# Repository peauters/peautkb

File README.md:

# Peautkb

## Intro
This is my first foray into custom built mechanical keyboards. I designed this as a mini project to get into pcb design and embedded code in `rust`. 

It has been awesome.

## Details
This board takes a lot of inspiration from the [Corne](https://github.com/foostan/crkbd) and [Kyria](https://blog.splitkb.com/blog/introducing-the-kyria) boards. 

I really liked the 3 rows from the Corne, as well as the rotaries from the Kyria. I wanted a single row thumb cluster and a column stager that fitted my hands. In then end, I ended up with what is in this repo.

## Firmware
Before I really had much info about open source keyboards, I decided I wanted to write my own firmware in `rust`. A well supported chip and board is the (WeAct MiniSTM32F4x1)[https://github.com/WeActTC/MiniSTM32F4x1] aka "the blackpill".

This board has a different footprint to a Pro Micro, which in hindsight has probably made this board very niche. I know of other blackpill boards (like the [Grandiceps](https://shop.tokas.co.uk/product/grandiceps-split-keyboard-kit/?v=79cba1185463)), but they seem limited at the moment.

The firmware is custom, written in `rust` using the [keyberon](https://github.com/TeXitoi/keyberon) as a base. At the moment, it manages communication between each side, the ssd1306 displays and has code to enable media keys in a second usb HID report. The most important feature is bongo cat animated displays. Thank you to [dancarrol](https://github.com/dancarroll/qmk-bongo) for the inspiration.

### How to build the firmware
- Install rust (see [here](https://www.rust-lang.org/tools/install))
- Install the compile target for the black-pills `rustup target install thumbv7em-none-eabihf`
- Install binutils to create a binary file `cargo install cargo-binutils` and `rustup component add llvm-tools-preview` 
- Build the binary `cargo objcopy --release -- -O binary out.bin`
- Put the black-pill in dfu boot loader. Hold the `NRST` and `BOOT0` buttons at the same time, then let go of `NRST` while still holding `BOOT0` button for a second longer.
- Check you can see it with `lsusb`
- Flash with dfu-util or similar
- Repeat for both sides

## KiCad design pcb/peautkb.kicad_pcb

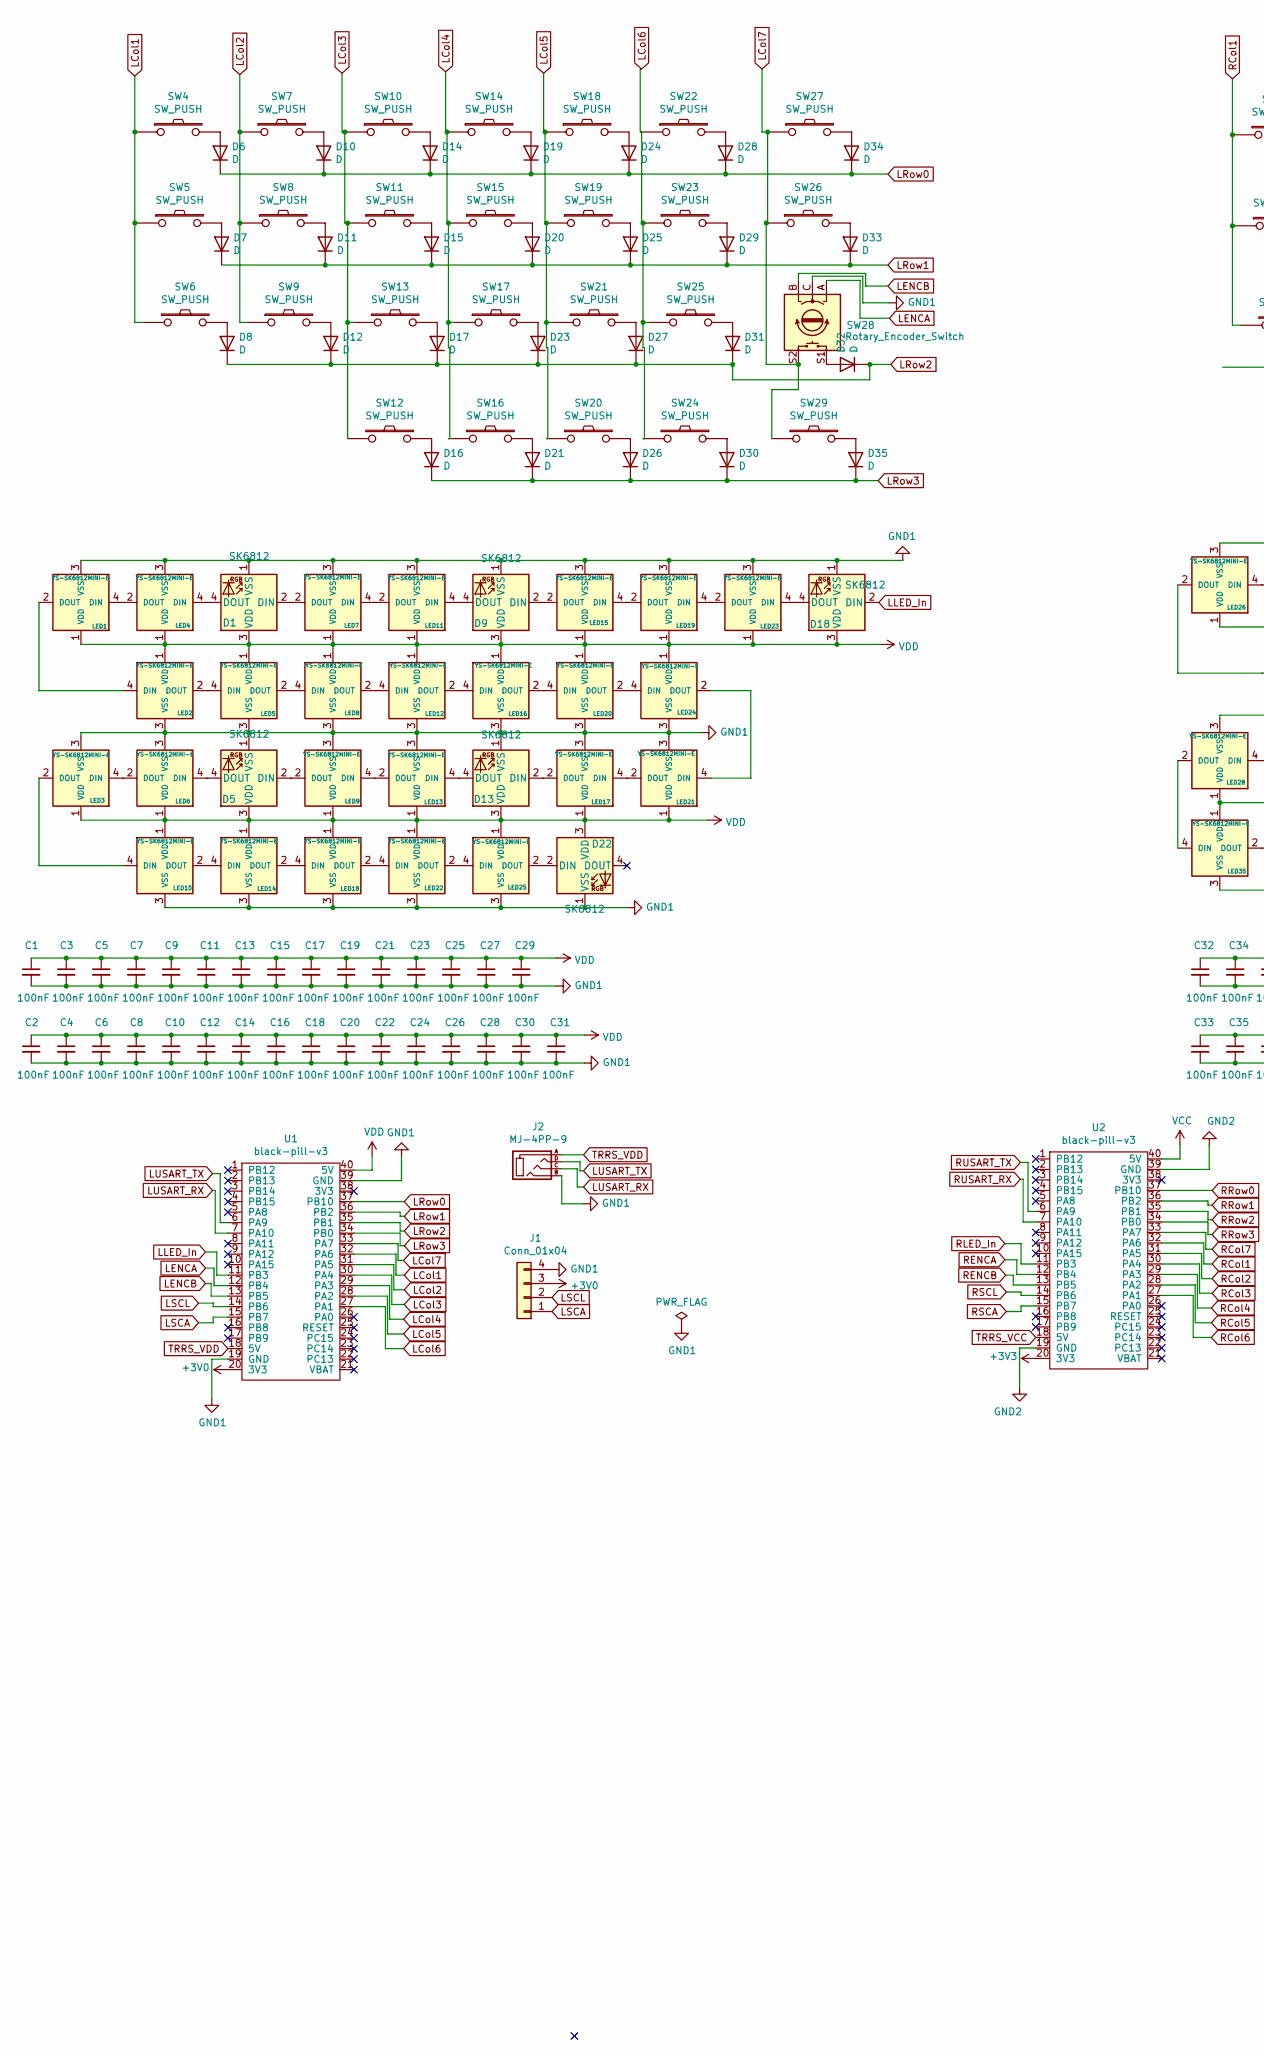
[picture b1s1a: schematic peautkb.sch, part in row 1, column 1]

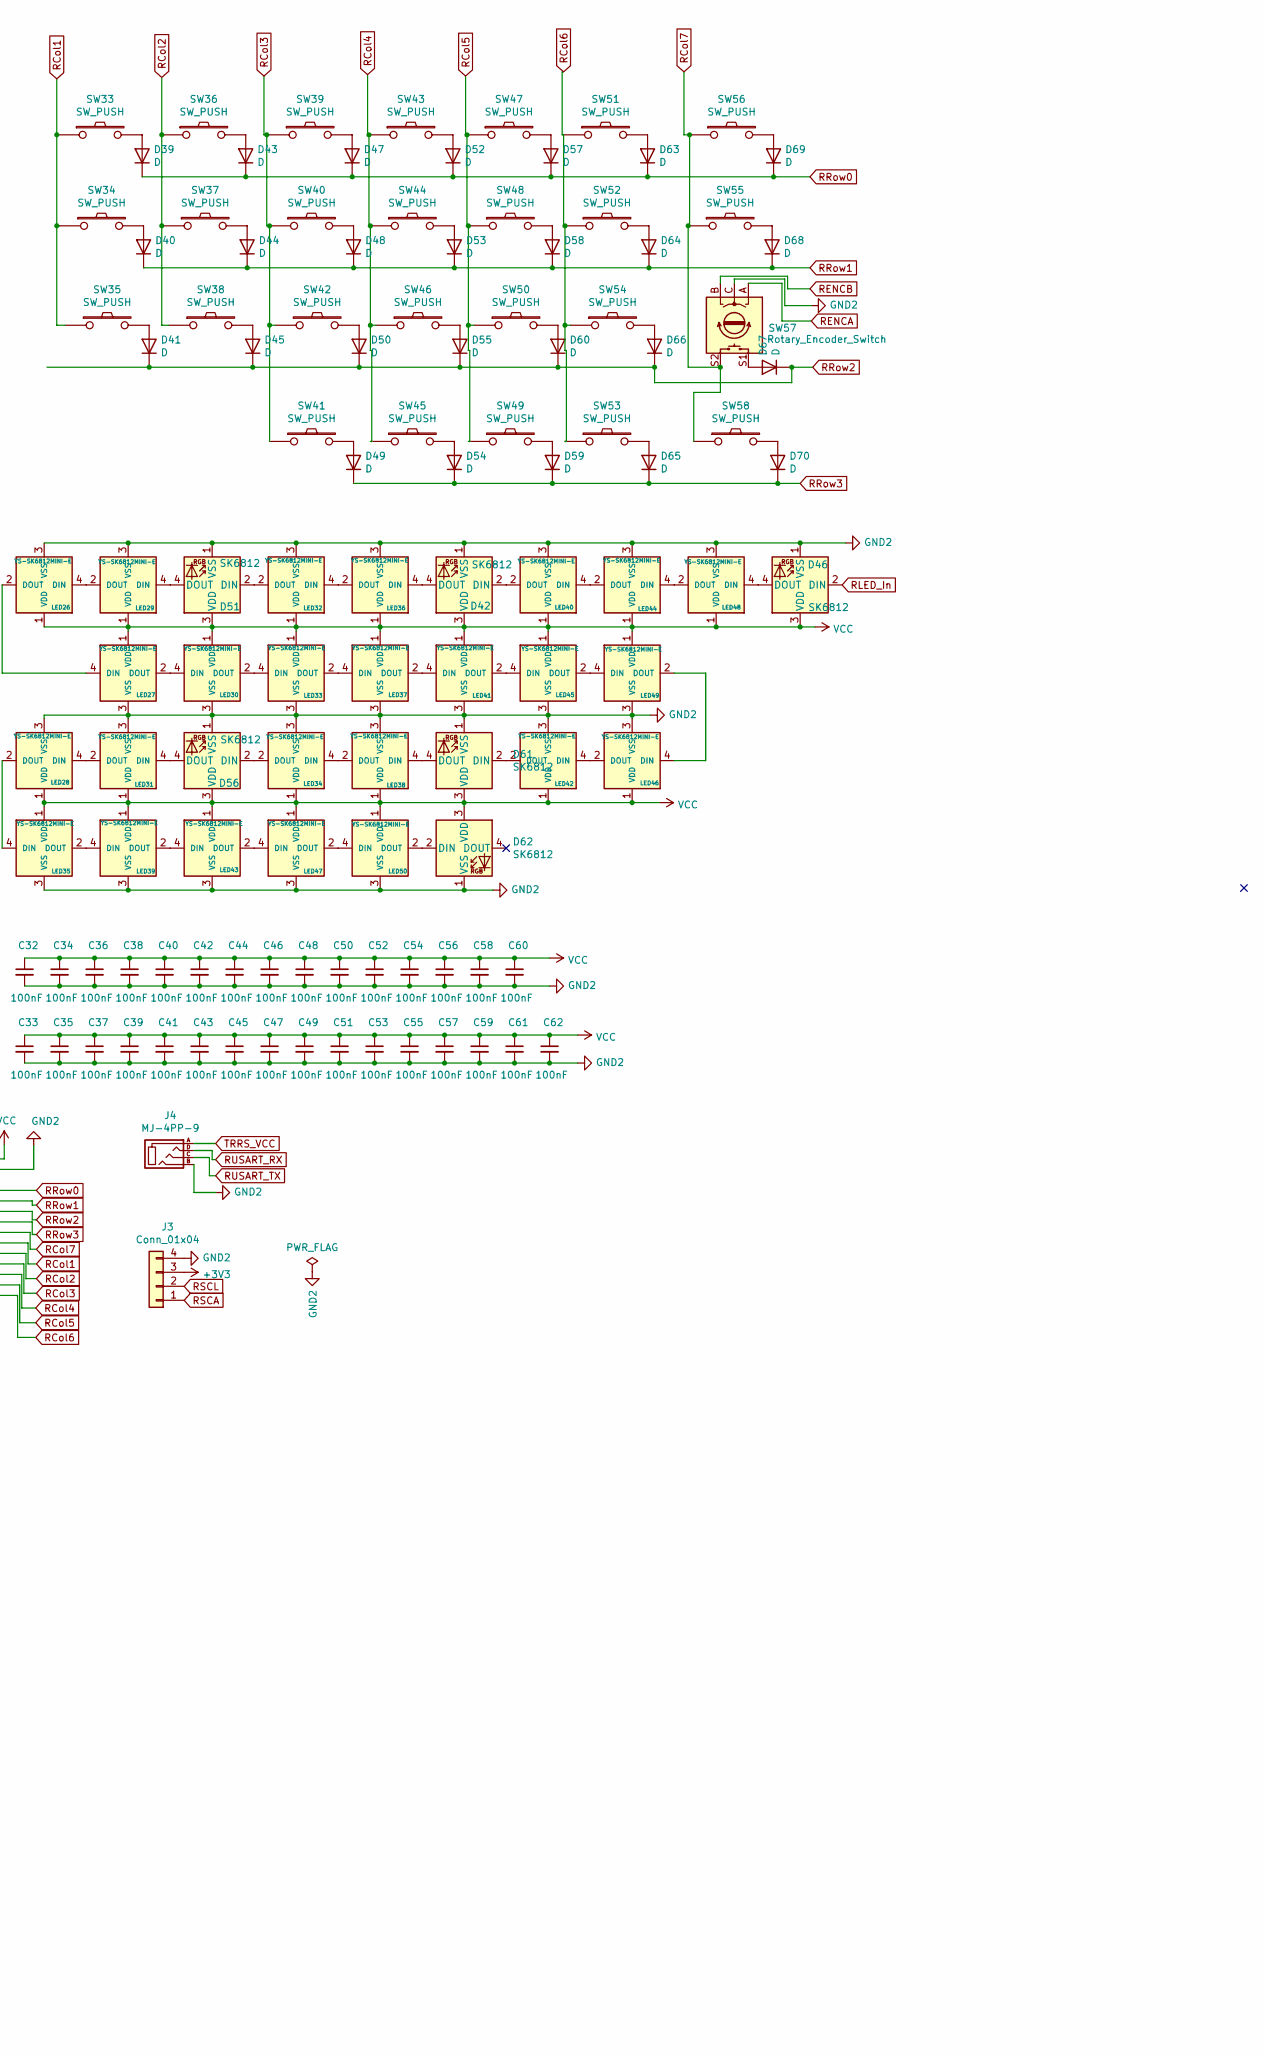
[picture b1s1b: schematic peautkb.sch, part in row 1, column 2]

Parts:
C1, C2, C3, C4, C5, C6, C7, C8, C9, C10, C11, C12, C13, C14, C15, C16, C17, C18, C19, C20, C21, C22, C23, C24, C25, C26, C27, C28, C29, C30, C31, C32, C33, C34, C35, C36, C37, C38, C39, C40, C41, C42, C43, C44, C45, C46, C47, C48, C49, C50, C51, C52, C53, C54, C55, C56, C57, C58, C59, C60, C61, C62: 100nF; C_0805_2012Metric_Pad1.18x1.45mm_HandSolder
D1, D5, D9, D13, D18, D22, D42, D46, D51, D56, D61, D62: SK6812; LED_SK6812_PLCC4_5.0x5.0mm_P3.2mm
D6, D7, D8, D10, D11, D12, D14, D15, D16, D17, D19, D20, D21, D23, D24, D25, D26, D27, D28, D29, D30, D31, D32, D33, D34, D35, D39, D40, D41, D43, D44, D45, D47, D48, D49, D50, D52, D53, D54, D55, D57, D58, D59, D60, D63, D64, D65, D66, D67, D68, D69, D70: D; D3_SMD_v2
J1, J3: Conn_01x04; OLED_1side
J2, J4: MJ-4PP-9
LED1, LED2, LED3, LED4, LED5, LED6, LED7, LED8, LED9, LED10, LED11, LED12, LED13, LED14, LED15, LED16, LED17, LED18, LED19, LED20, LED21, LED22, LED23, LED24, LED25, LED26, LED27, LED28, LED29, LED30, LED31, LED32, LED33, LED34, LED35, LED36, LED37, LED38, LED39, LED40, LED41, LED42, LED43, LED44, LED45, LED46, LED47, LED48, LED49, LED50: YS-SK6812MINI-E
SW4, SW5, SW6, SW7, SW8, SW9, SW10, SW11, SW12, SW13, SW14, SW15, SW16, SW17, SW18, SW19, SW20, SW21, SW22, SW23, SW24, SW25, SW26, SW27, SW29, SW33, SW34, SW35, SW36, SW37, SW38, SW39, SW40, SW41, SW42, SW43, SW44, SW45, SW46, SW47, SW48, SW49, SW50, SW51, SW52, SW53, SW54, SW55, SW56, SW58: SW_PUSH; CherryMX_Hotswap
SW28, SW57: Rotary_Encoder_Switch; RotaryEncoder_Alps_EC11E-Switch_Vertical_H20mm
U1, U2: black-pill-v3

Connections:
+3V0: J1.3, U1.20 (3V3)
+3V3: J3.3, U2.20 (3V3)
GND1: C1.2, C2.2, C3.2, C4.2, C5.2, C6.2, C7.2, C8.2, C9.2, C10.2, C11.2, C12.2, C13.2, C14.2, C15.2, C16.2, C17.2, C18.2, C19.2, C20.2, C21.2, C22.2, C23.2, C24.2, C25.2, C26.2, C27.2, C28.2, C29.2, C30.2, C31.2, D1.1 (VSS), D5.1 (VSS), D9.1 (VSS), D13.1 (VSS), D18.1 (VSS), D22.1 (VSS), J1.4, J2.B, LED1.3 (VSS), LED2.3 (VSS), LED3.3 (VSS), LED4.3 (VSS), LED5.3 (VSS), LED6.3 (VSS), LED7.3 (VSS), LED8.3 (VSS), LED9.3 (VSS), LED10.3 (VSS), LED11.3 (VSS), LED12.3 (VSS), LED13.3 (VSS), LED14.3 (VSS), LED15.3 (VSS), LED16.3 (VSS), LED17.3 (VSS), LED18.3 (VSS), LED19.3 (VSS), LED20.3 (VSS), LED21.3 (VSS), LED22.3 (VSS), LED23.3 (VSS), LED24.3 (VSS), LED25.3 (VSS), SW28.C, U1.19 (GND), U1.39 (GND)
GND2: C32.2, C33.2, C34.2, C35.2, C36.2, C37.2, C38.2, C39.2, C40.2, C41.2, C42.2, C43.2, C44.2, C45.2, C46.2, C47.2, C48.2, C49.2, C50.2, C51.2, C52.2, C53.2, C54.2, C55.2, C56.2, C57.2, C58.2, C59.2, C60.2, C61.2, C62.2, D42.1 (VSS), D46.1 (VSS), D51.1 (VSS), D56.1 (VSS), D61.1 (VSS), D62.1 (VSS), J3.4, J4.B, LED26.3 (VSS), LED27.3 (VSS), LED28.3 (VSS), LED29.3 (VSS), LED30.3 (VSS), LED31.3 (VSS), LED32.3 (VSS), LED33.3 (VSS), LED34.3 (VSS), LED35.3 (VSS), LED36.3 (VSS), LED37.3 (VSS), LED38.3 (VSS), LED39.3 (VSS), LED40.3 (VSS), LED41.3 (VSS), LED42.3 (VSS), LED43.3 (VSS), LED44.3 (VSS), LED45.3 (VSS), LED46.3 (VSS), LED47.3 (VSS), LED48.3 (VSS), LED49.3 (VSS), LED50.3 (VSS), SW57.C, U2.19 (GND), U2.39 (GND)
LCol1: SW4.1, SW5.1, SW6.1, U1.32 (PA6)
LCol2: SW7.1, SW8.1, SW9.1, U1.31 (PA5)
LCol3: SW10.1, SW11.1, SW12.1, SW13.1, U1.30 (PA4)
LCol4: SW14.1, SW15.1, SW16.1, SW17.1, U1.29 (PA3)
LCol5: SW18.1, SW19.1, SW20.1, SW21.1, U1.28 (PA2)
LCol6: SW22.1, SW23.1, SW24.1, SW25.1, U1.27 (PA1)
LCol7: SW26.1, SW27.1, SW28.S2, SW29.1, U1.33 (PA7)
LENCA: SW28.A, U1.12 (PB4)
LENCB: SW28.B, U1.13 (PB5)
LLED_In: D18.2 (DIN), U1.11 (PB3)
LRow0: D6.1 (K), D10.1 (K), D14.1 (K), D19.1 (K), D24.1 (K), D28.1 (K), D34.1 (K), U1.37 (PB10)
LRow1: D7.1 (K), D11.1 (K), D15.1 (K), D20.1 (K), D25.1 (K), D29.1 (K), D33.1 (K), U1.36 (PB2)
LRow2: D8.1 (K), D12.1 (K), D17.1 (K), D23.1 (K), D27.1 (K), D31.1 (K), D32.1 (K), U1.35 (PB1)
LRow3: D16.1 (K), D21.1 (K), D26.1 (K), D30.1 (K), D35.1 (K), U1.34 (PB0)
LSCA: J1.1, U1.15 (PB7)
LSCL: J1.2, U1.14 (PB6)
LUSART_RX: J2.C, U1.7 (PA10)
LUSART_TX: J2.D, U1.6 (PA9)
unnamed: D1.2 (DIN), LED7.2 (DOUT)
unnamed: D1.4 (DOUT), LED4.4 (DIN)
unnamed: D5.2 (DIN), LED9.2 (DOUT)
unnamed: D5.4 (DOUT), LED6.4 (DIN)
unnamed: D6.2 (A), SW4.2
unnamed: D7.2 (A), SW5.2
unnamed: D8.2 (A), SW6.2
unnamed: D9.2 (DIN), LED15.2 (DOUT)
unnamed: D9.4 (DOUT), LED11.4 (DIN)
unnamed: D10.2 (A), SW7.2
unnamed: D11.2 (A), SW8.2
unnamed: D12.2 (A), SW9.2
unnamed: D13.2 (DIN), LED17.2 (DOUT)
unnamed: D13.4 (DOUT), LED13.4 (DIN)
unnamed: D14.2 (A), SW10.2
unnamed: D15.2 (A), SW11.2
unnamed: D16.2 (A), SW12.2
unnamed: D17.2 (A), SW13.2
unnamed: D18.4 (DOUT), LED23.4 (DIN)
unnamed: D19.2 (A), SW14.2
unnamed: D20.2 (A), SW15.2
unnamed: D21.2 (A), SW16.2
unnamed: D22.2 (DIN), LED25.2 (DOUT)
unnamed: D23.2 (A), SW17.2
unnamed: D24.2 (A), SW18.2
unnamed: D25.2 (A), SW19.2
unnamed: D26.2 (A), SW20.2
unnamed: D27.2 (A), SW21.2
unnamed: D28.2 (A), SW22.2
unnamed: D29.2 (A), SW23.2
unnamed: D30.2 (A), SW24.2
unnamed: D31.2 (A), SW25.2
unnamed: D32.2 (A), SW28.S1
unnamed: D33.2 (A), SW26.2
unnamed: D34.2 (A), SW27.2
unnamed: D35.2 (A), SW29.2
unnamed: D39.2 (A), SW33.2
unnamed: D40.2 (A), SW34.2
unnamed: D41.2 (A), SW35.2
unnamed: D42.2 (DIN), LED40.2 (DOUT)
unnamed: D42.4 (DOUT), LED36.4 (DIN)
unnamed: D43.2 (A), SW36.2
unnamed: D44.2 (A), SW37.2
unnamed: D45.2 (A), SW38.2
unnamed: D46.4 (DOUT), LED48.4 (DIN)
unnamed: D47.2 (A), SW39.2
unnamed: D48.2 (A), SW40.2
unnamed: D49.2 (A), SW41.2
unnamed: D50.2 (A), SW42.2
unnamed: D51.2 (DIN), LED32.2 (DOUT)
unnamed: D51.4 (DOUT), LED29.4 (DIN)
unnamed: D52.2 (A), SW43.2
unnamed: D53.2 (A), SW44.2
unnamed: D54.2 (A), SW45.2
unnamed: D55.2 (A), SW46.2
unnamed: D56.2 (DIN), LED34.2 (DOUT)
unnamed: D56.4 (DOUT), LED31.4 (DIN)
unnamed: D57.2 (A), SW47.2
unnamed: D58.2 (A), SW48.2
unnamed: D59.2 (A), SW49.2
unnamed: D60.2 (A), SW50.2
unnamed: D61.2 (DIN), LED42.2 (DOUT)
unnamed: D61.4 (DOUT), LED38.4 (DIN)
unnamed: D62.2 (DIN), LED50.2 (DOUT)
unnamed: D63.2 (A), SW51.2
unnamed: D64.2 (A), SW52.2
unnamed: D65.2 (A), SW53.2
unnamed: D66.2 (A), SW54.2
unnamed: D67.2 (A), SW57.S1
unnamed: D68.2 (A), SW55.2
unnamed: D69.2 (A), SW56.2
unnamed: D70.2 (A), SW58.2
unnamed: LED1.2 (DOUT), LED2.4 (DIN)
unnamed: LED1.4 (DIN), LED4.2 (DOUT)
unnamed: LED2.2 (DOUT), LED5.4 (DIN)
unnamed: LED3.4 (DIN), LED6.2 (DOUT)
unnamed: LED5.2 (DOUT), LED8.4 (DIN)
unnamed: LED10.2 (DOUT), LED14.4 (DIN)
unnamed: LED3.2 (DOUT), LED10.4 (DIN)
unnamed: LED7.4 (DIN), LED11.2 (DOUT)
unnamed: LED12.2 (DOUT), LED16.4 (DIN)
unnamed: LED8.2 (DOUT), LED12.4 (DIN)
unnamed: LED9.4 (DIN), LED13.2 (DOUT)
unnamed: LED14.2 (DOUT), LED18.4 (DIN)
unnamed: LED15.4 (DIN), LED19.2 (DOUT)
unnamed: LED16.2 (DOUT), LED20.4 (DIN)
unnamed: LED17.4 (DIN), LED21.2 (DOUT)
unnamed: LED18.2 (DOUT), LED22.4 (DIN)
unnamed: LED19.4 (DIN), LED23.2 (DOUT)
unnamed: LED20.2 (DOUT), LED24.4 (DIN)
unnamed: LED21.4 (DIN), LED24.2 (DOUT)
unnamed: LED22.2 (DOUT), LED25.4 (DIN)
unnamed: LED26.2 (DOUT), LED27.4 (DIN)
unnamed: LED26.4 (DIN), LED29.2 (DOUT)
unnamed: LED27.2 (DOUT), LED30.4 (DIN)
unnamed: LED28.2 (DOUT), LED35.4 (DIN)
unnamed: LED28.4 (DIN), LED31.2 (DOUT)
unnamed: LED30.2 (DOUT), LED33.4 (DIN)
unnamed: LED32.4 (DIN), LED36.2 (DOUT)
unnamed: LED33.2 (DOUT), LED37.4 (DIN)
unnamed: LED34.4 (DIN), LED38.2 (DOUT)
unnamed: LED35.2 (DOUT), LED39.4 (DIN)
unnamed: LED37.2 (DOUT), LED41.4 (DIN)
unnamed: LED39.2 (DOUT), LED43.4 (DIN)
unnamed: LED40.4 (DIN), LED44.2 (DOUT)
unnamed: LED41.2 (DOUT), LED45.4 (DIN)
unnamed: LED42.4 (DIN), LED46.2 (DOUT)
unnamed: LED43.2 (DOUT), LED47.4 (DIN)
unnamed: LED44.4 (DIN), LED48.2 (DOUT)
unnamed: LED45.2 (DOUT), LED49.4 (DIN)
unnamed: LED46.4 (DIN), LED49.2 (DOUT)
unnamed: LED47.2 (DOUT), LED50.4 (DIN)
RCol1: SW33.1, SW34.1, SW35.1, U2.32 (PA6)
RCol2: SW36.1, SW37.1, SW38.1, U2.31 (PA5)
RCol3: SW39.1, SW40.1, SW41.1, SW42.1, U2.30 (PA4)
RCol4: SW43.1, SW44.1, SW45.1, SW46.1, U2.29 (PA3)
RCol5: SW47.1, SW48.1, SW49.1, SW50.1, U2.28 (PA2)
RCol6: SW51.1, SW52.1, SW53.1, SW54.1, U2.27 (PA1)
RCol7: SW55.1, SW56.1, SW57.S2, SW58.1, U2.33 (PA7)
RENCA: SW57.A, U2.12 (PB4)
RENCB: SW57.B, U2.13 (PB5)
RLED_In: D46.2 (DIN), U2.11 (PB3)
RRow0: D39.1 (K), D43.1 (K), D47.1 (K), D52.1 (K), D57.1 (K), D63.1 (K), D69.1 (K), U2.37 (PB10)
RRow1: D40.1 (K), D44.1 (K), D48.1 (K), D53.1 (K), D58.1 (K), D64.1 (K), D68.1 (K), U2.36 (PB2)
RRow2: D41.1 (K), D45.1 (K), D50.1 (K), D55.1 (K), D60.1 (K), D66.1 (K), D67.1 (K), U2.35 (PB1)
RRow3: D49.1 (K), D54.1 (K), D59.1 (K), D65.1 (K), D70.1 (K), U2.34 (PB0)
RSCA: J3.1, U2.15 (PB7)
RSCL: J3.2, U2.14 (PB6)
RUSART_RX: J4.D, U2.7 (PA10)
RUSART_TX: J4.C, U2.6 (PA9)
TRRS_VCC: J4.A, U2.18 (5V)
TRRS_VDD: J2.A, U1.18 (5V)
VCC: C32.1, C33.1, C34.1, C35.1, C36.1, C37.1, C38.1, C39.1, C40.1, C41.1, C42.1, C43.1, C44.1, C45.1, C46.1, C47.1, C48.1, C49.1, C50.1, C51.1, C52.1, C53.1, C54.1, C55.1, C56.1, C57.1, C58.1, C59.1, C60.1, C61.1, C62.1, D42.3 (VDD), D46.3 (VDD), D51.3 (VDD), D56.3 (VDD), D61.3 (VDD), D62.3 (VDD), LED26.1 (VDD), LED27.1 (VDD), LED28.1 (VDD), LED29.1 (VDD), LED30.1 (VDD), LED31.1 (VDD), LED32.1 (VDD), LED33.1 (VDD), LED34.1 (VDD), LED35.1 (VDD), LED36.1 (VDD), LED37.1 (VDD), LED38.1 (VDD), LED39.1 (VDD), LED40.1 (VDD), LED41.1 (VDD), LED42.1 (VDD), LED43.1 (VDD), LED44.1 (VDD), LED45.1 (VDD), LED46.1 (VDD), LED47.1 (VDD), LED48.1 (VDD), LED49.1 (VDD), LED50.1 (VDD), U2.40 (5V)
VDD: C1.1, C2.1, C3.1, C4.1, C5.1, C6.1, C7.1, C8.1, C9.1, C10.1, C11.1, C12.1, C13.1, C14.1, C15.1, C16.1, C17.1, C18.1, C19.1, C20.1, C21.1, C22.1, C23.1, C24.1, C25.1, C26.1, C27.1, C28.1, C29.1, C30.1, C31.1, D1.3 (VDD), D5.3 (VDD), D9.3 (VDD), D13.3 (VDD), D18.3 (VDD), D22.3 (VDD), LED1.1 (VDD), LED2.1 (VDD), LED3.1 (VDD), LED4.1 (VDD), LED5.1 (VDD), LED6.1 (VDD), LED7.1 (VDD), LED8.1 (VDD), LED9.1 (VDD), LED10.1 (VDD), LED11.1 (VDD), LED12.1 (VDD), LED13.1 (VDD), LED14.1 (VDD), LED15.1 (VDD), LED16.1 (VDD), LED17.1 (VDD), LED18.1 (VDD), LED19.1 (VDD), LED20.1 (VDD), LED21.1 (VDD), LED22.1 (VDD), LED23.1 (VDD), LED24.1 (VDD), LED25.1 (VDD), U1.40 (5V)

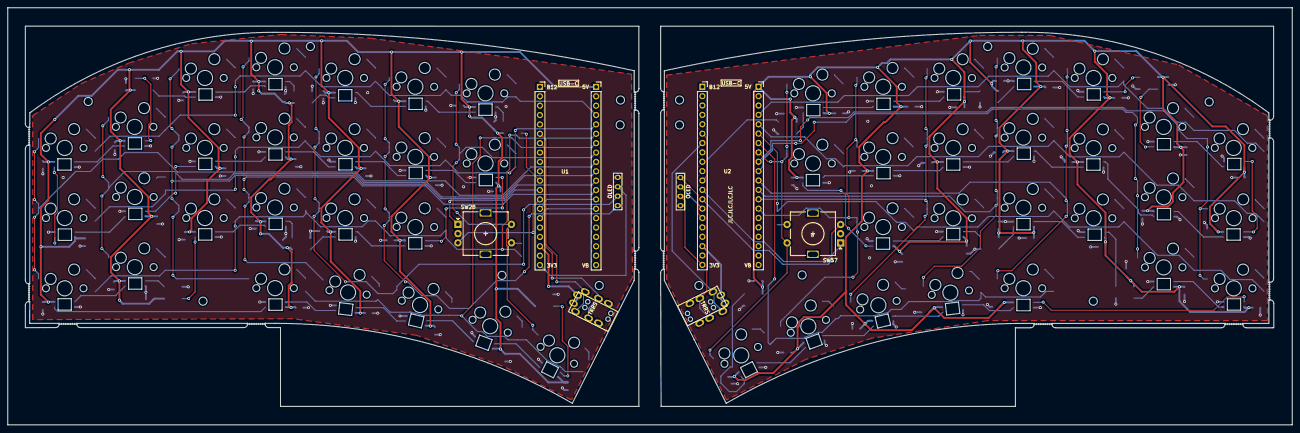
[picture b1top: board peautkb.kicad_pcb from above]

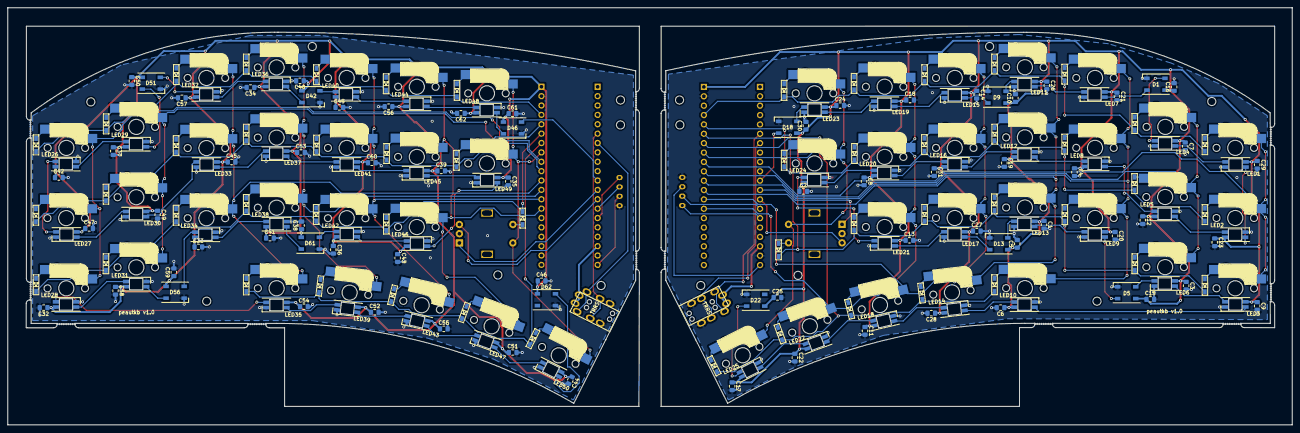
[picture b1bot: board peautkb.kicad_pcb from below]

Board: 2 copper layers, 348.0 x 113.0 mm, 248 parts (176 on the bottom side), 156 nets.

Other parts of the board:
Ref**: Val**; M2_HOLE_v2
Ref**#2, Ref**#3, Ref**#4, Ref**#5, Ref**#6, Ref**#7, Ref**#8, Ref**#9, Ref**#10, Ref**#11, Ref**#12, Ref**#13, Ref**#14: Val**; M2_HOLE_v2

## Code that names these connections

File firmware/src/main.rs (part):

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    const PID: u16 = 0x27db;

    pub struct Cols(
        gpioa::PA6<Input<PullUp>>,
        gpioa::PA5<Input<PullUp>>,
        gpioa::PA4<Input<PullUp>>,
        gpioa::PA3<Input<PullUp>>,
        gpioa::PA2<Input<PullUp>>,
        gpioa::PA1<Input<PullUp>>,
        gpioa::PA7<Input<PullUp>>,
    );
    impl_heterogenous_array! {
        Cols,
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        [0, 1, 2, 3, 4, 5, 6]
    }
    pub struct Rows(
        gpiob::PB10<Output<PushPull>>,
        gpiob::PB2<Output<PushPull>>,
        gpiob::PB1<Output<PushPull>>,
        gpiob::PB0<Output<PushPull>>,
    );
    impl_heterogenous_array! {
        Rows,
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        let tick_timer = timer::Timer::tim4(perfs.TIM4, 24.hz(), clocks);

        // I2C for SSD1306 display
        let pb6 = gpiob
            .pb6
            .into_alternate_af4()
            .internal_pull_up(true)
            .set_open_drain();
        let pb7 = gpiob
            .pb7
            .into_alternate_af4()
            .internal_pull_up(true)
            .set_open_drain();
        let display = OLED::new(perfs.I2C1, pb6, pb7, clocks);

        // Rotary encoder pins
        let pb4 = gpiob.pb4.into_pull_up_input();
        let mut pb5 = gpiob.pb5.into_pull_up_input();

        pb5.make_interrupt_source(&mut syscfg);
        pb5.enable_interrupt(&mut perfs.EXTI);
        pb5.trigger_on_edge(&mut perfs.EXTI, Edge::RISING_FALLING);

        let rotary = Rotary::new(pb4, pb5, (3, 0), (3, 1));

        // USB keyboard
        let usb = otg_fs::USB {
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            .build();

        // Inter-board comms
        let pa9 = gpioa.pa9.into_alternate_af7();
        let pa10 = gpioa.pa10.into_alternate_af7();

        let (tx, rx) = create_comms(perfs.USART1, pa9, pa10, clocks);

        // Keyberon setup
        let matrix = Matrix::new(
            Cols(
                gpioa.pa6.into_pull_up_input(),
                gpioa.pa5.into_pull_up_input(),
                gpioa.pa4.into_pull_up_input(),
                gpioa.pa3.into_pull_up_input(),
                gpioa.pa2.into_pull_up_input(),
                gpioa.pa1.into_pull_up_input(),
                gpioa.pa7.into_pull_up_input(),
            ),
            Rows(
                gpiob.pb10.into_push_pull_output(),
                gpiob.pb2.into_push_pull_output(),
                gpiob.pb1.into_push_pull_output(),
                gpiob.pb0.into_push_pull_output(),
            ),
        )
        .unwrap();
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
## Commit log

2021-03-27 before pcb layout
2021-03-27 removes extra col
2021-03-28 left side traces completed
2021-03-29 aadded decoup caps to LHS
2021-03-29 finished RHS
2021-03-30 generate gerbers
2021-03-31 added practice pads
2021-04-01 logo and final OLED placement
2021-04-02 pcb tweaks
2021-04-02 initial firmware with rtic timer working
2021-04-02 adds registering as a keyboard
2021-04-10 updated rotary encoder pins to avoid crystal
2021-04-11 LED working, usb hid working, display working (on reset), example interrupt on a1
2021-04-12 serail interface working
2021-04-14 before 4->2 layer rework
2021-04-14 re-worked with copper pours for gnd and 5v routed, re-routed the LHS completely
2021-04-19 submitted pcbs - i hope
2021-04-19 display and serial split out
2021-04-28 debugging i2c issues
2021-04-29 first working firmware
2021-05-05 adds rotary encoder and first attempt at media keys
2021-05-06 media keys working with dual reports
2021-05-07 adds cmd-tab on right rotary layer 1
2021-05-07 adds ctrl-tab on the left encoder layer 1, pushes events into rotary from main
2021-05-07 adds ctrl,cmd held status to info
2021-05-07 adds menu
2021-05-10 current layer
2021-05-10 bongo
2021-05-10 working apart from intermitant stuck keys
2021-05-11 set correct memory for mcu
2021-05-11 move encoders to interrupt driven, fix tick() being called appropriately
2021-05-12 fixes spacing on info screen
2021-05-18 adds case stls
2021-05-18 fix keymap for CS
2021-05-18 add back bongo for left hand side
2021-05-18 adds README.md
2021-05-18 cleans up pcb files
2021-05-18 adds license
2021-06-14 updates keymap
2021-06-16 moves symbols to their own layers
2021-06-16 only open menu on primary
2021-06-16 adds solid rgb at start
2021-06-17 leds with menu for changing mode and colour
2021-06-19 adds flashiing instructions
2021-06-20 disables oled and leds
2021-06-23 Update Cargo.toml
    made it do git stuff
2021-06-25 dma spi working leds example
2021-06-25 changes to ensure builds locally
2021-06-25 leds working with dma spi
2021-06-28 fade led, keymap update and LED sleep
2021-06-28 sleep OLEDs
2021-11-14 adds right hand stls
2022-03-02 moves to git based deps for changes + fade led pattern
